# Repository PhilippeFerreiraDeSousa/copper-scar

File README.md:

# Copper Scar

**Native board experiments, implementation branches, prompts, and candidate history:** [Hackathon work index](docs/hackathon/README.md).

The sections below describe the earlier scaffold. See the index for the actual KiCad/Freerouting demo pipeline and separate JITX research.

**One-liner:** Agent loop that scars PCBGolf attempts — Weave spans, hard gates, official comma.ai score — for CoreWeave Hacks.

## Loop

1. Observe baseline / last scar  
2. Plan (Weave `plan`)  
3. Act via tool forge (`place` / `route`) or **sim board** scars  
4. Check hard gates (fail-closed)  
5. Score with the **official** formula  
6. Write a scar JSON  
7. Compare and keep best gates-ok run  

Contract: [`copper_scar/loop/contract.md`](copper_scar/loop/contract.md)

## Score formula (exact)

```
score = volume_mm3 + 50 * vias + 5000 * copper_layers
volume = bbox_width * bbox_height * thickness_mm
```

Source: [comma.ai leaderboard — PCBGolf](https://comma.ai/leaderboard#pcbgolf_challenge)  
PCBGolf repo (link only, do not clone into this tree): https://github.com/commaai/PCBGolf

## Hard gates

Fail-closed. Missing flag = fail. See `copper_scar.harness.gates.HARD_GATES`:

- `drc_clean`
- `erc_clean`
- `netlist_match`
- `fab_stackup_ok`
- `min_trace_clearance`
- `via_annular_ok`
- `outline_closed`

Do not ship a scar to the “best” board unless `gates_ok` is true.

## Weave spans

Minimum spans recorded on each scar / demo pass:

| Span | Role |
|------|------|
| `loop.pass.{i}` | One observe → act → evaluate → improve cycle |
| `observe.load` | Load stock baseline |
| `act.plan` / `act.apply_scar` | Intent + apply typed scar |
| `evaluate.drc` / `evaluate.gates` / `evaluate.score` | DRC, hard gates, official score |
| `improve.scar.write` | Persist scar |

Each live span carries attributes: `score`, `best_score`, `drc_count`, `gates_ok`, `scar_id`, `policy_version`.

### Live Weave — 90s Best Use of Weave script

Judges look for **all three**: (1) an agent that is actually instrumented, (2) a real eval on a dataset you built, (3) an online Signal on live traces.

The offline demo is unchanged without Weave. Live tracing is a no-op unless the extra is installed **and** `WANDB_API_KEY` is set.

```bash
pip install -e ".[weave]"
export WANDB_API_KEY=...          # https://wandb.ai/authorize
export WEAVE_PROJECT=philippe-fdesousa/copper-scar  # user entity (org blocks bare project names)

# W&B Inference credits (kickoff form): fill the form circulated at
# CoreWeave Hacks so Serverless Inference can power UI Signals/Monitors.
# Event page: https://wandb.ai/site/resources/events/coreweave-hacks-agent-loops-hackathon-with-weights-biases-and-agi-house/

copper-scar demo                  # 1. explicit weave.init + loop spans/ops
copper-scar eval                  # 2. built dataset → Weave Evaluation
```

`--weave-project` overrides `WEAVE_PROJECT`. `--no-weave` forces the offline path even if a key is present.

When tracing is on, commands print a Weave UI URL:

`https://wandb.ai/<entity>/copper-scar/weave`

**90s film beats**

| t | Show |
|---|------|
| 0–25 | `copper-scar demo` — Traces: `copper_scar.agent_pass` / `loop.pass.{i}` → `observe` → `act` → `evaluate` → `improve` |
| 25–55 | Expand pass 2: `act.apply_scar`, `evaluate.drc` / `gates` / `score`, attributes `score`, `best_score`, `drc_count`, `gates_ok`, `scar_id`, `policy_version` |
| 55–75 | `copper-scar eval` — Evaluations → `copper-scar-loop-eval` on dataset `copper-scar-boards` (`evals/dataset/`, 8 BoardState fixtures we built) |
| 75–90 | **Signal:** Traces → Scores column (live `apply_scorer`), then Monitors (below) |

**Attach / enable the online Signal in the Weave UI**

Code already applies three programmatic Signals to every `loop.pass.{i}` call:

- `score_improves_vs_baseline` — official score dropped vs the fixture/stock baseline
- `gates_ok_when_scar_applied` — after a scar is applied, hard gates pass
- `drc_cleared_after_scar` — after a scar is applied, DRC is clean

To attach the same criteria as a live Monitor / UI Signal (uses W&B Inference credits):

1. Run `copper-scar demo` once so ops appear
2. Weave sidebar → **Monitors** → **New Monitor** (or **Browse signals** → **Create custom signal**)
3. Operations: `copper_scar.agent_pass` and/or `loop.pass.1` (repeat for `.2` / `.3` if listed separately)
4. Sampling: 100%
5. Judge model: a **Serverless Inference** model (credits from the kickoff form)
6. Scoring prompt: see `SIGNAL_UI_PROMPT` in [`copper_scar/eval/scorers.py`](copper_scar/eval/scorers.py)
7. Create → re-run `copper-scar demo` → Traces shows the Signal tags / Scores column

Without the key or without the weave extra, `copper-scar demo` and `copper-scar eval` still run identically offline (no network, no crash).

## Scar schema

JSON Schema: [`copper_scar/scars/schema.json`](copper_scar/scars/schema.json)  
Example: [`copper_scar/scars/examples/scar_012.json`](copper_scar/scars/examples/scar_012.json)  
Store helpers: `copper_scar.scars.store`

A scar holds `scar_id`, `metrics`, `score`, `gates`, optional typed `rule` (`keepout` / `min_clearance`), `weave.span_ids`, and `tools_used`.

## Sim board (no KiCad)

`copper_scar.sim.board` provides a deterministic AABB board:

- Parts + outline DRC (min 0.5 mm clearance)
- Actions: `shrink_outline`, `move_part`, `apply_keepout_scar`
- Official score from `volume_mm3 = w * h * thickness`

Stock baseline: [`baselines/stock.json`](baselines/stock.json) (overlapping parts + oversized outline).

## Tool forge

Adapters live under [`copper_scar/tools/registry/`](copper_scar/tools/README.md).  
Empty at ship; fill during the hack. Loop calls only registered tools.

## 90s demo

```bash
cd /workspace/copper-scar
python3 -m venv .venv
.venv/bin/pip install -e ".[dev]"
.venv/bin/copper-scar demo
.venv/bin/copper-scar eval
```

What you should see:

1. **Pass 1** — stock board with DRC issues; Weave-style spans; writes typed scar (`scar_001`)
2. **Pass 2** — loads/applies scar with credit `scar_001 → keepout U1`; plan changes
3. **Pass 3** — gates OK and official score **lower** than pass 1
4. **Eval** — 8 built fixtures in [`evals/dataset/`](evals/dataset/); table of expected vs loop output

Artifacts:

- `demos/out/pass_timeline.txt` — summary table + spans
- `demos/out/board_pass_{1,2,3}.svg` — board snapshots

Also:

```bash
.venv/bin/pytest -q
.venv/bin/copper-scar score baselines/stock.json
```

See [`demos/pass_timeline.md`](demos/pass_timeline.md) for the narrated beat sheet.

## Ship / cut

**Ship (CoreWeave Hacks)**

- `copper-scar score` / `copper-scar loop` / `copper-scar demo` / `copper-scar eval`
- Exact official score
- Deterministic sim closed loop → scar JSON + SVG timeline
- Explicit Weave spans/ops around observe/act/evaluate/improve
- Built eval dataset + Weave Evaluation + online Signals
- Hard gates module + schema

**Cut**

- Full PCBGolf / KiCad automation
- Mentra paths

## Dual timeline

| Track | When | Outcome |
|-------|------|---------|
| **CoreWeave Hacks** | This weekend | Harness + demo + Weave story |
| **Oct 12 $1k** | Oct 12 | Gates-ok scars with real measured deltas |

## Mentra — out of scope

Mentra / AR glasses integration is **out of scope** for Copper Scar. Do not block the CoreWeave or Oct 12 tracks on Mentra work.

## How to run

```bash
cd /workspace/copper-scar
.venv/bin/pip install -e ".[dev]"
.venv/bin/pytest -q
.venv/bin/copper-scar score baselines/stock.json
.venv/bin/copper-scar loop --scar-id scar_000 --out-dir scars_out
.venv/bin/copper-scar demo
.venv/bin/copper-scar eval
```

Requires Python ≥ 3.11.

## License

Apache-2.0 — see [`LICENSE`](LICENSE).

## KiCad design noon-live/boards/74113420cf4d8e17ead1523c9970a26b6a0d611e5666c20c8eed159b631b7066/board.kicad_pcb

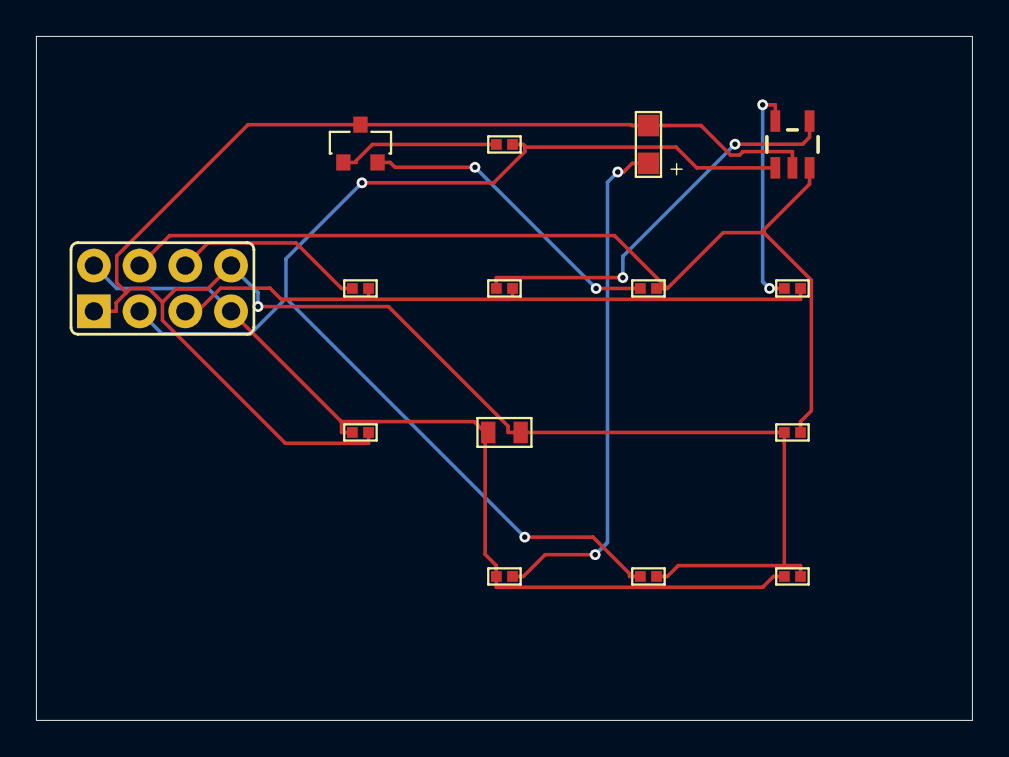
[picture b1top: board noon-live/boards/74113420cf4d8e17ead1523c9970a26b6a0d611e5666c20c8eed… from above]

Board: 2 copper layers, 52.0 x 38.0 mm, 15 parts (0 on the bottom side), 11 nets.

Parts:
C5, C46: 100nF; 0402-C
C50: 10u; 0805-C
J4: CAN; 2X04
LED6: CH1_PWR; CHIPLED
LED10: LED-CC-GREEN-RED-AM23ESG; SOT23-3
Q2: NFET-DUAL-COMMON-SOURCE-QS5K2; SOT23-5
R19: 100k; 0402-R
R74: 3k3; 0402-R
R78, R98: 10k; 0402-R
R82, R83, R91: 100; 0402-R
R90: 1k; 0402-R

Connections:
CH1_SBU1: J4.5, R19.2, R90.2, R91.2
CH1_SBU1_IGN: J4.3, Q2.1 (G1), R78.1, R83.2
CH1_SBU1_RELAY: J4.4, Q2.3 (G2), R82.2, R98.2
EXT_5V: C5.1, C46.1, C50.1, J4.2, J4.7, R74.1
EXT_SENSE: J4.6, R19.1
GND: C5.2, C46.2, C50.2, J4.1, J4.8, LED6.C, LED10.3 (C), Q2.2 (S), R78.2, R98.1
unnamed: LED6.A, R74.2
unnamed: LED10.2 (AG), R82.1
unnamed: LED10.1 (AR), R83.1
unnamed: Q2.5 (D1), R90.1
unnamed: Q2.4 (D2), R91.1

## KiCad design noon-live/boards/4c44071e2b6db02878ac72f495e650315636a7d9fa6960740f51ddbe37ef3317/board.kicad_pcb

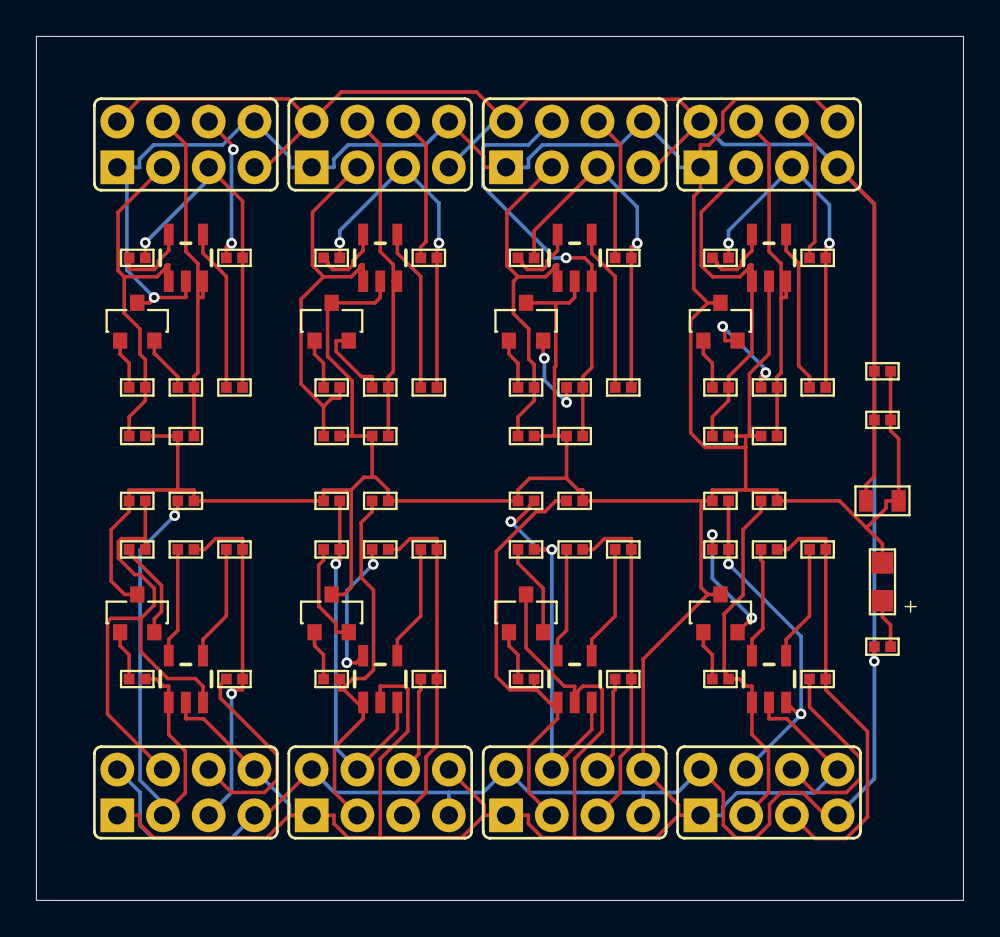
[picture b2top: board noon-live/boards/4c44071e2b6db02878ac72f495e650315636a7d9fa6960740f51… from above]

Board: 2 copper layers, 51.5 x 48.0 mm, 85 parts (0 on the bottom side), 67 nets.

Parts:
C5, C46: 100nF; 0402-C
C50: 10u; 0805-C
J101, J102, J103, J104, J105, J106, J107, J108: HEADER_2x04_2.54mm_POPULATED; 2X04
LED6: CH1_PWR; CHIPLED
LED10, LED11, LED12, LED13, LED14, LED15, LED16, LED17: LED-CC-GREEN-RED-AM23ESG; SOT23-3
Q2, Q3, Q4, Q5, Q6, Q7, Q8, Q9: NFET-DUAL-COMMON-SOURCE-QS5K2; SOT23-5
R13, R14, R15, R16, R17, R18, R19, R20: 100k; 0402-R
R74: 3k3; 0402-R
R78, R79, R80, R81, R98, R99, R100, R101, R102, R103, R104, R105, R122, R123, R124, R125: 10k; 0402-R
R82, R83, R84, R85, R86, R87, R88, R89, R91, R93, R95, R97, R106, R107, R108, R109, R110, R111, R112, R113, R115, R117, R119, R121: 100; 0402-R
R90, R92, R94, R96, R114, R116, R118, R120: 1k; 0402-R

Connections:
CH1_SBU1: J101.5, R19.2, R90.2, R91.2
CH1_SBU1_IGN: J101.3, Q2.1 (G1), R78.1, R83.2
CH1_SBU1_RELAY: J101.4, Q2.3 (G2), R82.2, R98.2
CH1_SBU2: J105.5, R20.2, R114.2, R115.2
CH1_SBU2_IGN: J105.3, Q6.1 (G1), R102.1, R107.2
CH1_SBU2_RELAY: J105.4, Q6.3 (G2), R106.2, R122.2
CH2_SBU1: J102.5, R15.2, R92.2, R93.2
CH2_SBU1_IGN: J102.3, Q3.1 (G1), R79.1, R85.2
CH2_SBU1_RELAY: J102.4, Q3.3 (G2), R84.2, R99.2
CH2_SBU2: J106.5, R13.2, R116.2, R117.2
CH2_SBU2_IGN: J106.3, Q7.1 (G1), R103.1, R109.2
CH2_SBU2_RELAY: J106.4, Q7.3 (G2), R108.2, R123.2
CH3_SBU1: J103.5, R17.2, R94.2, R95.2
CH3_SBU1_IGN: J103.3, Q4.1 (G1), R80.1, R87.2
CH3_SBU1_RELAY: J103.4, Q4.3 (G2), R86.2, R100.2
CH3_SBU2: J107.5, R18.2, R118.2, R119.2
CH3_SBU2_IGN: J107.3, Q8.1 (G1), R104.1, R111.2
CH3_SBU2_RELAY: J107.4, Q8.3 (G2), R110.2, R124.2
CH4_SBU1: J104.5, R16.2, R96.2, R97.2
CH4_SBU1_IGN: J104.3, Q5.1 (G1), R81.1, R89.2
CH4_SBU1_RELAY: J104.4, Q5.3 (G2), R88.2, R101.2
CH4_SBU2: J108.5, R14.2, R120.2, R121.2
CH4_SBU2_IGN: J108.3, Q9.1 (G1), R105.1, R113.2
CH4_SBU2_RELAY: J108.4, Q9.3 (G2), R112.2, R125.2
EXT_5V: C5.1, C46.1, C50.1, J101.2, J101.7, J102.2, J102.7, J103.2, J103.7, J104.2, J104.7, J105.2, J105.7, J106.2, J106.7, J107.2, J107.7, J108.2, J108.7, R74.1
GND: C5.2, C46.2, C50.2, J101.1, J101.8, J102.1, J102.8, J103.1, J103.8, J104.1, J104.8, J105.1, J105.8, J106.1, J106.8, J107.1, J107.8, J108.1, J108.8, LED6.C, LED10.3 (C), LED11.3 (C), LED12.3 (C), LED13.3 (C), LED14.3 (C), LED15.3 (C), LED16.3 (C), LED17.3 (C), Q2.2 (S), Q3.2 (S), Q4.2 (S), Q5.2 (S), Q6.2 (S), Q7.2 (S), Q8.2 (S), Q9.2 (S), R78.2, R79.2, R80.2, R81.2, R98.1, R99.1, R100.1, R101.1, R102.2, R103.2, R104.2, R105.2, R122.1, R123.1, R124.1, R125.1
unnamed: LED6.A, R74.2
unnamed: LED10.2 (AG), R82.1
unnamed: LED10.1 (AR), R83.1
unnamed: LED11.2 (AG), R84.1
unnamed: LED11.1 (AR), R85.1
unnamed: LED12.2 (AG), R86.1
unnamed: LED12.1 (AR), R87.1
unnamed: LED13.2 (AG), R88.1
unnamed: LED13.1 (AR), R89.1
unnamed: LED14.2 (AG), R106.1
unnamed: LED14.1 (AR), R107.1
unnamed: LED15.2 (AG), R108.1
unnamed: LED15.1 (AR), R109.1
unnamed: LED16.2 (AG), R110.1
unnamed: LED16.1 (AR), R111.1
unnamed: LED17.2 (AG), R112.1
unnamed: LED17.1 (AR), R113.1
unnamed: Q2.5 (D1), R90.1
unnamed: Q2.4 (D2), R91.1
unnamed: Q3.5 (D1), R92.1
unnamed: Q3.4 (D2), R93.1
unnamed: Q4.5 (D1), R94.1
unnamed: Q4.4 (D2), R95.1
unnamed: Q5.5 (D1), R96.1
unnamed: Q5.4 (D2), R97.1
unnamed: Q6.5 (D1), R114.1
unnamed: Q6.4 (D2), R115.1
unnamed: Q7.5 (D1), R116.1
unnamed: Q7.4 (D2), R117.1
unnamed: Q8.5 (D1), R118.1
unnamed: Q8.4 (D2), R119.1
unnamed: Q9.5 (D1), R120.1
unnamed: Q9.4 (D2), R121.1
unnamed: J103.6, R17.1
unnamed: J107.6, R18.1
unnamed: J101.6, R19.1
unnamed: J105.6, R20.1
unnamed: J106.6, R13.1
unnamed: J108.6, R14.1
unnamed: J102.6, R15.1
unnamed: J104.6, R16.1
